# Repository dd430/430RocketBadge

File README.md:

430RocketBadge
==============

Code Repository for the 430RocketBadge

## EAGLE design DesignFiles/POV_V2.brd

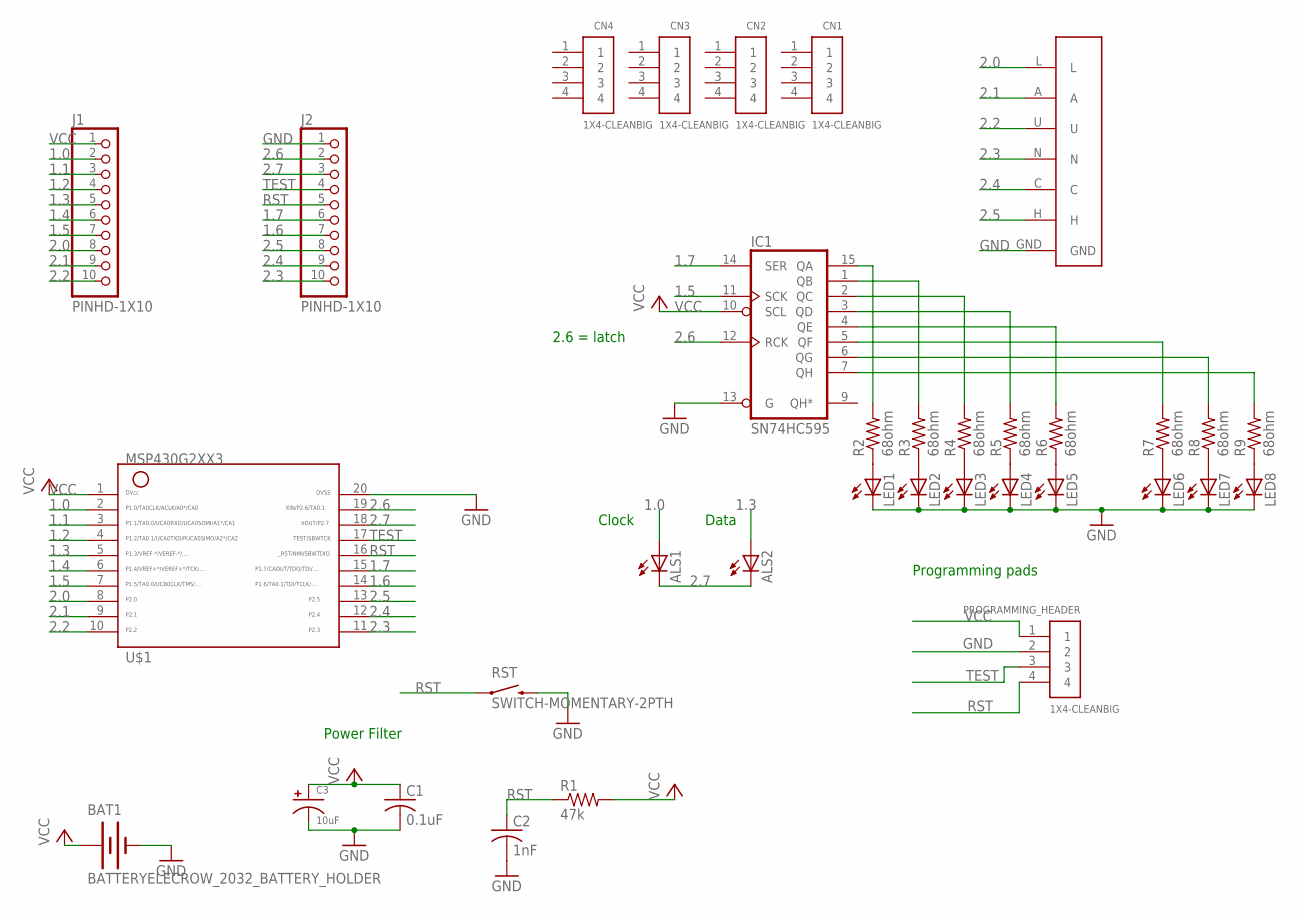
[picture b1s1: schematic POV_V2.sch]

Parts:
ALS1, ALS2: LED3MM
BAT1: BATTERYELECROW_2032_BATTERY_HOLDER; BATTCON_20MM_4LEGS
C1: 0.1uF; C025-024X044
C2: 1nF; C025-024X044
C3: 10uF; E2,5-5
CN1, CN2, CN3, CN4: 1X4-CLEANBIG; 1X04-CLEANBIG
IC1: SN74HC595; DIL16
J1, J2: PINHD-1X10; 1X10-BIG
LED1, LED2, LED3, LED4, LED5, LED6, LED7, LED8: LED3MM
PROGRAMMING_HEADER: 1X4-CLEANBIG; 1X04-CLEANBIG
R1: 47k; 0204/7
R2, R3, R4, R5, R6, R7, R8, R9: 68ohm; 0204/7
RST: SWITCH-MOMENTARY-2PTH; TACTILE-PTH
U$1: G2553; N20
U$5: LAUNCH_SLIDER; LAUNCHYOURDESIGN_CAPT_SLIDER

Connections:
1.0: ALS1.A, J1.2, U$1.2
1.1: J1.3, U$1.3
1.2: J1.4, U$1.4
1.3: ALS2.A, J1.5, U$1.5
1.4: J1.6, U$1.6
1.5: IC1.11 (SCK), J1.7, U$1.7
1.6: J2.7, U$1.14
1.7: IC1.14 (SER), J2.6, U$1.15
2.0: J1.8, U$1.8, U$5.L
2.1: J1.9, U$1.9, U$5.A
2.2: J1.10, U$1.10, U$5.U
2.3: J2.10, U$1.11, U$5.N
2.4: J2.9, U$1.12, U$5.C
2.5: J2.8, U$1.13, U$5.H
2.6: IC1.12 (RCK), J2.2, U$1.19
2.7: ALS1.K (C), ALS2.K (C), J2.3, U$1.18
GND: BAT1.GND (-), C1.2, C2.2, C3.-, IC1.8 (GND), IC1.13 (G), J2.1, LED1.K (C), LED2.K (C), LED3.K (C), LED4.K (C), LED5.K (C), LED6.K (C), LED7.K (C), LED8.K (C), PROGRAMMING_HEADER.2, RST.3 (2), RST.4 (2), U$1.20, U$5.GND
unnamed: LED1.A, R2.1
unnamed: LED2.A, R3.1
unnamed: LED3.A, R4.1
unnamed: LED4.A, R5.1
unnamed: LED5.A, R6.1
unnamed: IC1.15 (QA), R2.2
unnamed: IC1.1 (QB), R3.2
unnamed: IC1.2 (QC), R4.2
unnamed: IC1.3 (QD), R5.2
unnamed: IC1.4 (QE), R6.2
unnamed: LED6.A, R7.1
unnamed: LED7.A, R8.1
unnamed: LED8.A, R9.1
unnamed: IC1.5 (QF), R7.2
unnamed: IC1.6 (QG), R8.2
unnamed: IC1.7 (QH), R9.2
RST: C2.1, J2.5, PROGRAMMING_HEADER.4, R1.1, RST.1, RST.2 (1), U$1.16
TEST: J2.4, PROGRAMMING_HEADER.3, U$1.17
VCC: BAT1.VCC1 (+), BAT1.VCC2 (+), BAT1.VCC3 (+), C1.1, C3.+, IC1.10 (SCL), IC1.16 (VCC), J1.1, PROGRAMMING_HEADER.1, R1.2, U$1.1

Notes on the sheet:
Power Filter
Programming pads
2.6 = latch
Clock
Data

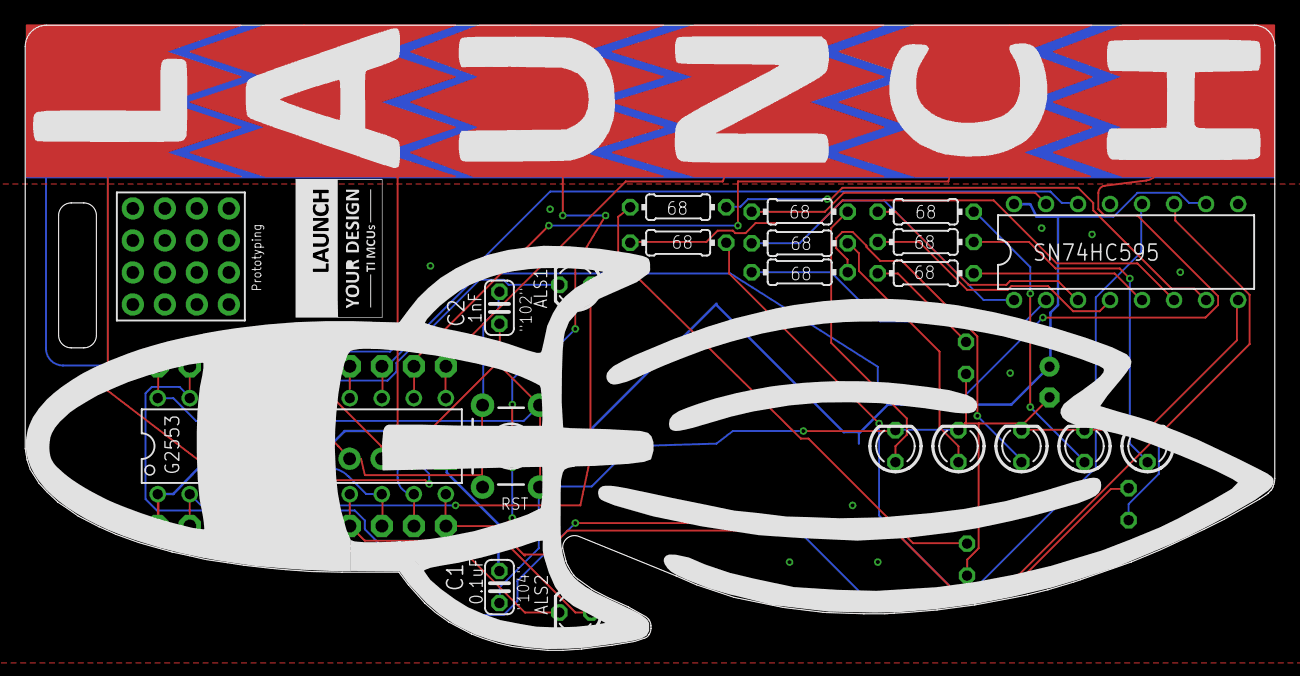
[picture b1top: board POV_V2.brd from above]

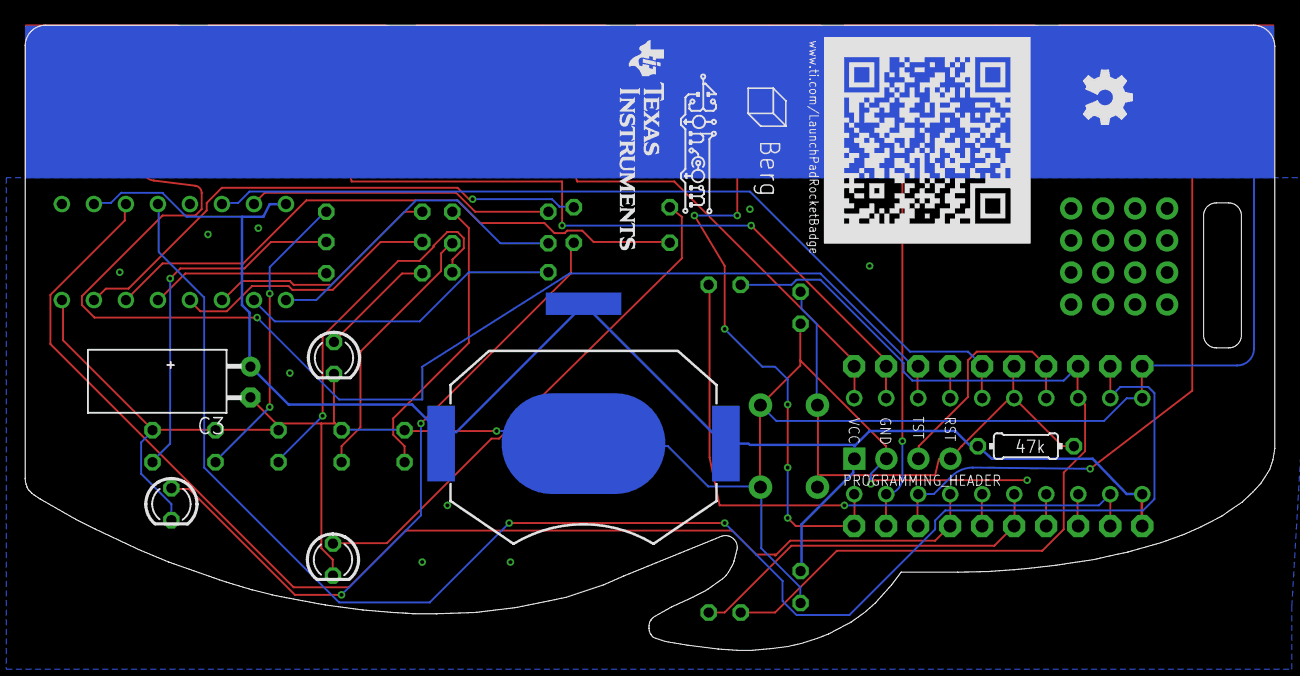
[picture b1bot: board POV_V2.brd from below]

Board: 2 copper layers, 99.2 x 49.6 mm, 42 parts (12 on the bottom side), 36 nets.

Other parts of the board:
U$2: ROCKET_WIDER_V3
U$3: OSHW_FILLX150_NOTEXT
U$4: TI_BADGE_QR
U$6: LAUNCH_CIRCUIT_OVERLAY
U$7: BERG_TI_SILK
U$8: 43OH_CIRCUIT_LOGO_LONG
U$9: LYD_FULL
U$10: LOGO16_TPLACE

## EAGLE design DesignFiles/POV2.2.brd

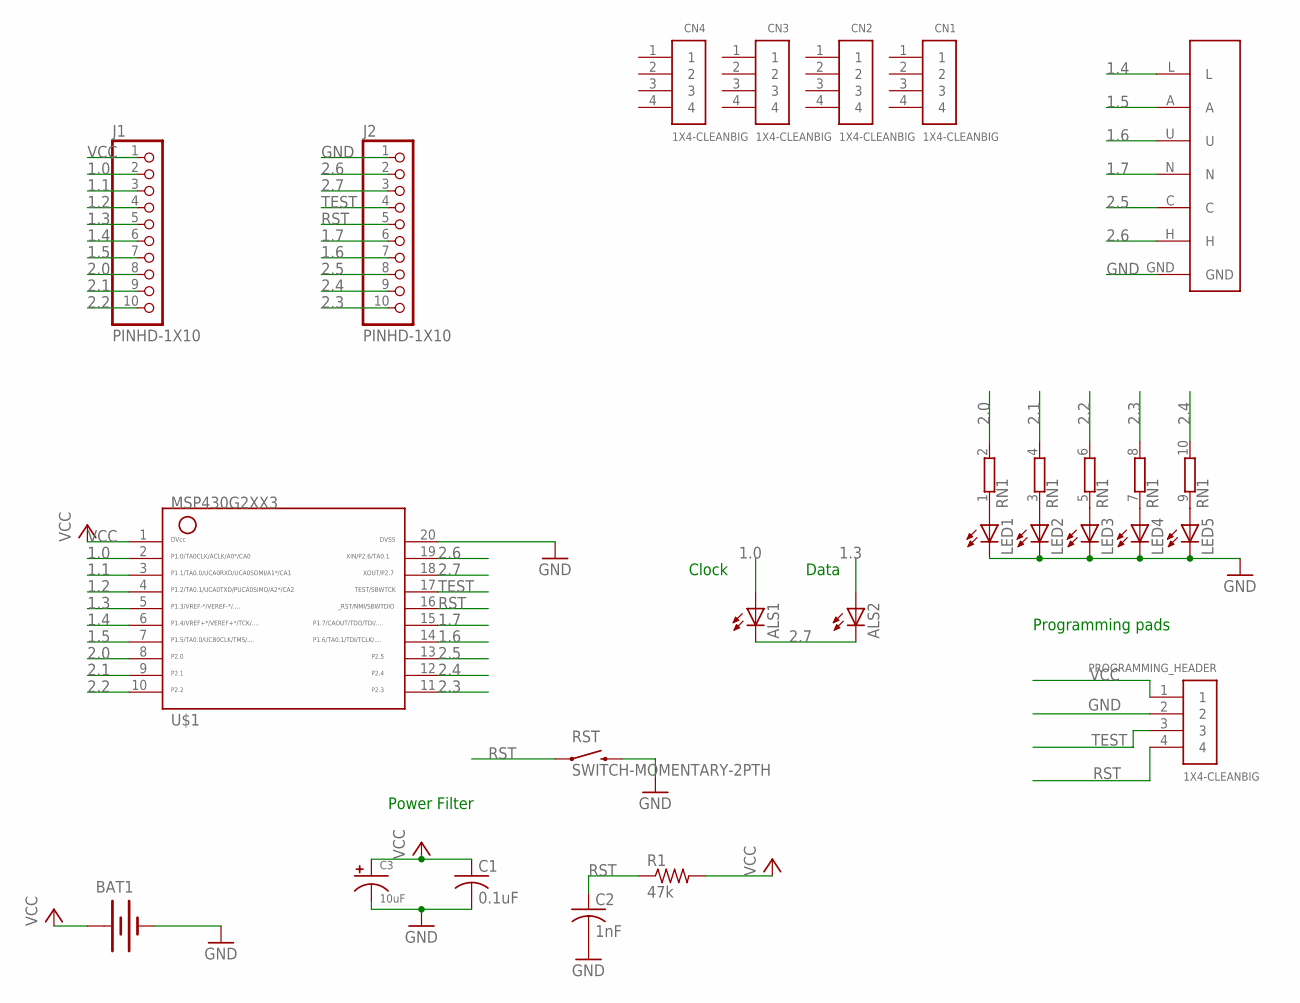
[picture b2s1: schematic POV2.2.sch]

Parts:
ALS1, ALS2: LED3MM
BAT1: BATTERYELECROW_2032_BATTERY_HOLDER; BATTCON_20MM_4LEGS
C1: 0.1uF; C025-024X044
C2: 1nF; C025-024X044
C3: 10uF; E2,5-5
CN1, CN2, CN3, CN4: 1X4-CLEANBIG; 1X04-CLEANBIG
J1, J2: PINHD-1X10; 1X10-BIG
LED1, LED2, LED3, LED4, LED5: LED3MM
PROGRAMMING_HEADER: 1X4-CLEANBIG; 1X04-CLEANBIG
R1: 47k; 0204/7
RN1: E5RP; SIL10
RST: SWITCH-MOMENTARY-2PTH; TACTILE-PTH
U$1: G2553; N20
U$5: LAUNCH_SLIDER; LAUNCHYOURDESIGN_CAPT_SLIDER

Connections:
1.0: ALS1.A, J1.2, U$1.2
1.1: J1.3, U$1.3
1.2: J1.4, U$1.4
1.3: ALS2.A, J1.5, U$1.5
1.4: J1.6, U$1.6, U$5.L
1.5: J1.7, U$1.7, U$5.A
1.6: J2.7, U$1.14, U$5.U
1.7: J2.6, U$1.15, U$5.N
2.0: J1.8, RN1.2, U$1.8
2.1: J1.9, RN1.4 (2), U$1.9
2.2: J1.10, RN1.6 (2), U$1.10
2.3: J2.10, RN1.8 (2), U$1.11
2.4: J2.9, RN1.10 (2), U$1.12
2.5: J2.8, U$1.13, U$5.C
2.6: J2.2, U$1.19, U$5.H
2.7: ALS1.K (C), ALS2.K (C), J2.3, U$1.18
GND: BAT1.GND (-), C1.2, C2.2, C3.-, J2.1, LED1.K (C), LED2.K (C), LED3.K (C), LED4.K (C), LED5.K (C), PROGRAMMING_HEADER.2, RST.3 (2), RST.4 (2), U$1.20, U$5.GND
unnamed: LED1.A, RN1.1
unnamed: LED2.A, RN1.3 (1)
unnamed: LED3.A, RN1.5 (1)
unnamed: LED4.A, RN1.7 (1)
unnamed: LED5.A, RN1.9 (1)
RST: C2.1, J2.5, PROGRAMMING_HEADER.4, R1.1, RST.1, RST.2 (1), U$1.16
TEST: J2.4, PROGRAMMING_HEADER.3, U$1.17
VCC: BAT1.VCC1 (+), BAT1.VCC2 (+), C1.1, C3.+, J1.1, PROGRAMMING_HEADER.1, R1.2, U$1.1

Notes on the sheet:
Power Filter
Programming pads
Clock
Data

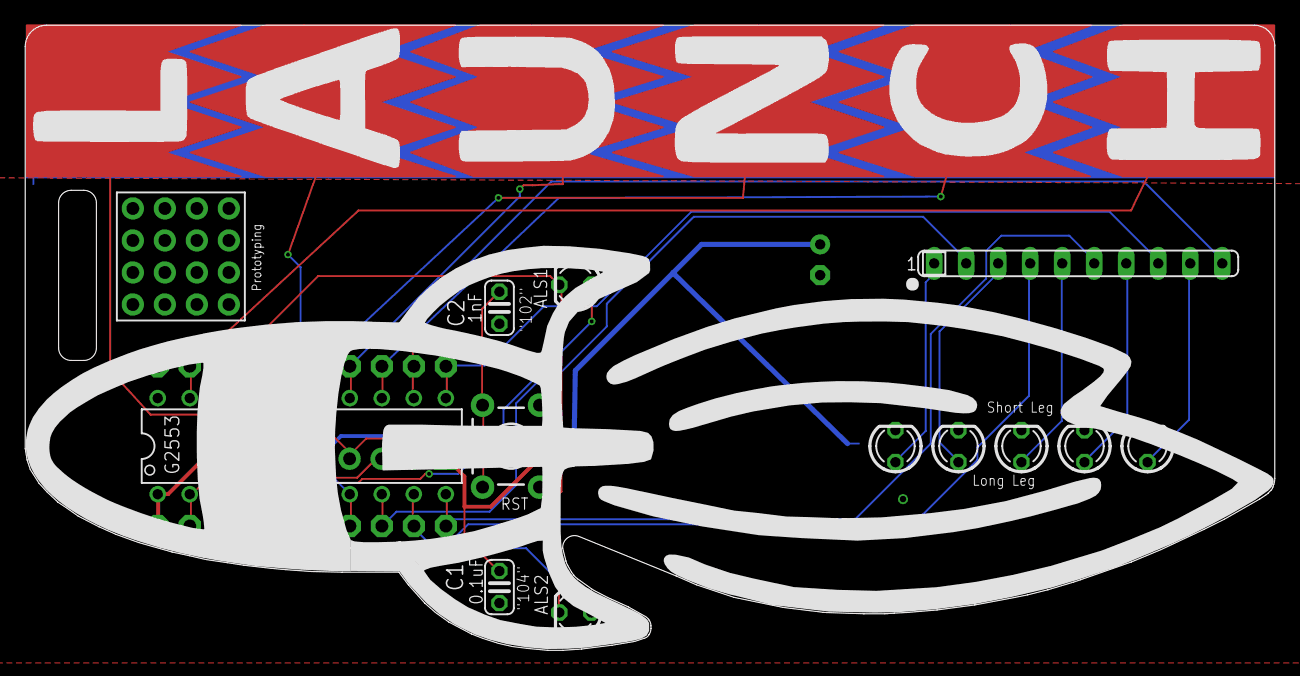
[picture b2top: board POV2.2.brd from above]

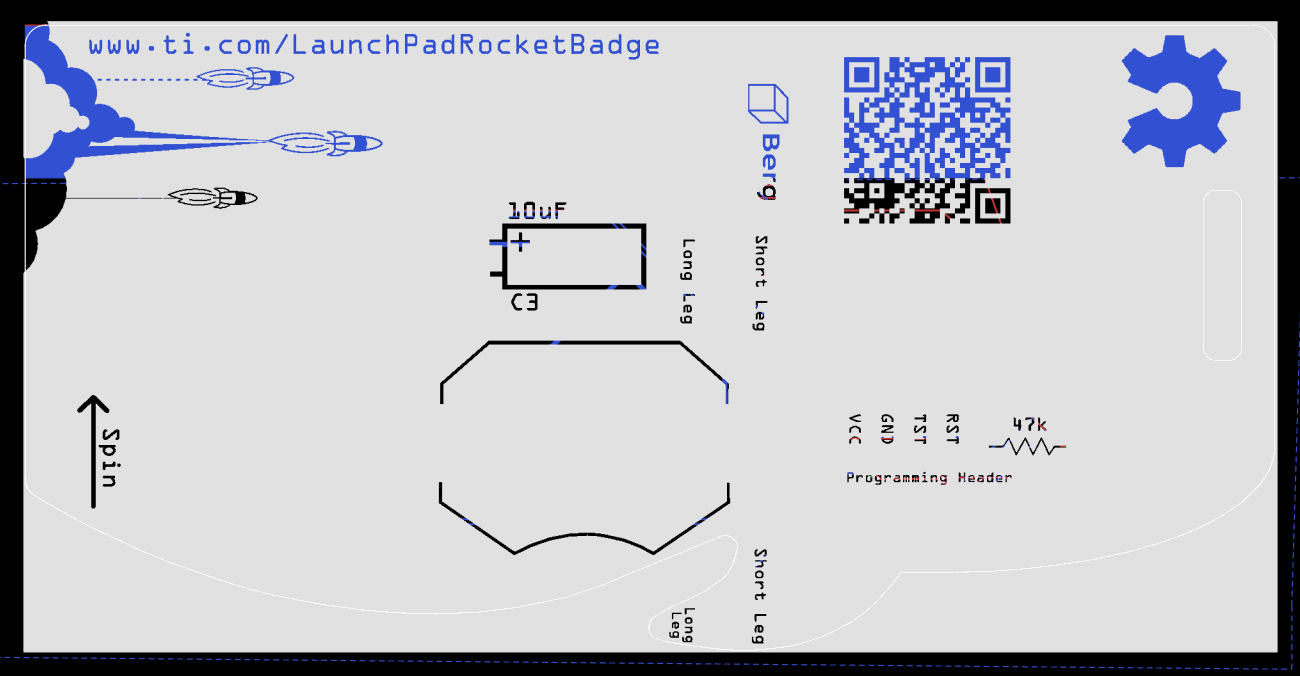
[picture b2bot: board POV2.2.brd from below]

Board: 2 copper layers, 99.2 x 49.6 mm, 26 parts (5 on the bottom side), 25 nets.

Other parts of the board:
U$2: ROCKET_WIDER_V3
U$4: TI_BADGE_QR
U$6: LAUNCH_CIRCUIT_OVERLAY2

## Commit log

2014-02-13 Basic POV example
    Initial work on getting a good POV output
2014-02-13 Data Transfer + LEDs
    Basic data transfer from a browser + debug output to LEDs
2014-02-13 Browser-based updates
    Initial work on a browser-based data transfer mechanism
2014-02-15 Working cap touch test
    Code is a bit too sensitive right now and only reads one button at a
    time - needs some work
2014-02-15 Updating browser flashing
    Works pretty decent now. Communication scheme works well.
2014-02-15 Updated data transfer
    Included transfer validation/scheme. Needs to be updated with code to
    write to reserved flash.
2014-02-25 Almost ready to fully read/write from flash
    Checking in before I fully switch over to flash
2014-02-26 Fully working browser -> flash
2014-02-28 Decreasing sensitivity
    this doesn't pick up touches on the side of the badge anymore
2014-02-28 [ADDED] EAGLE design ilfiles
2014-03-01 Switched reverse silk to polygons
2014-03-01 Missed the middle of a couple of characters
2014-03-01 Some logo tweaks to the board
2014-03-02 [ADDED\ ] CapTOuch tuning project
2014-03-06 Adding gerbers for first production run
2014-04-05 Committing files from board v1.0 before moving to v2
2014-04-10 Changes for the V2 badge board
2014-04-10 Updating to newest eagle files
2014-04-26 Adding in start of final project
    Including tuned cap touch pads, code to move from POV to Cap Touch Demo.
    Code for flashing new messages included but not activated
2014-04-26 [ADDED] CCS exlcude files for .gitignore
2014-04-26 [ADDED] CCS project config files for the final code
2014-04-27 [UPDATED] Captouch Demo: light up more than one LEDs as finger slides down from L to H, creating the flame effect on the LaunchPad rocket fume. L-A-U-N-C->H ---> more flame --> launch.
2014-04-29 added transitions and programming
    ability to switch from POV to cap touch demo (bottom-up) or programming
    (top-down)
2014-04-29 correcting odd sync issue
    sync conflict caused some problems with github for some reason
2014-04-30 Fixed some bugs in the programming
2014-04-30 Implementing "special feature"
2014-05-02 Special feature done, new set of messages
2014-05-07 Adding a stop button to prevent a long wait if transmission fails
2014-05-08 Changed one of the default messages slightly. Slight css tweak to the programming page
2014-05-08 Code that's being flashed on the first 500 badges
2014-05-11 Updated tuning application to reflect the current hardware and use LEDs to provide tuning feedback.
2014-07-09 Had incorrect version of board uploaded
    Correcting uploaded eagle board

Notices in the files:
parts and their libraries:
Sparkfun: Licensing: CC v3.0 Share-Alike You are welcome to use this library for commercial purposes.
